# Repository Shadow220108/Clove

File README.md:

<h1 align="center">
  <br>

  <br>
  Clove
  <br>
</h1>
<h3 align="center">
First ever paw shaped tamagotchi, with 4 buttons, LEDs, screen and battery 
</h3>

| Render | 
| --- |
|  | 

The case is made to be paw shaped, designed in two halves which are supposed to be put together with 4 different M3x8mm screws.  
It has a slot to hold the battery, 4 screw holes to hold and tighten the PCB! The top case features 4 holes for the buttons and 
a space for the screen.  

| Zine |
| --- |
| .png) |

## PCB Design 
|  |
|--- |  

 The PCB is 2 layers with dimensions under 100 by 100mm, it is designed to be in a paw shape has some cool 
 silkscreen with red color, cause red colored PCBs are cool.  

 ### All the PCB files are [here](https://github.com/Shadow220108/Clove/tree/main/PCB) 

| PCB design |
| --- |
| .png) | .png) |

## Schematics  

Here are the schematic designs,

| Schematics |
| --- |
|  |

## Why was it made?  

It was made for fallout hackclub with the amazing guide made by @Tanuki ( huge credits to him ) 

## How you can get one for yourself? 

That is pretty easy, 

1. Order all the parts going through the BOM
2. Start by soldering all the components on to the PCB
3. Put the buttons in the holes, screw the PCB to the case and screw both the halves together
4. Flash the Xiao with firmware and boom
5. Start playing with your tamagotchi

## BOM  

|Product                       |Description                                      |Quantity   |Unit Price  |Link      |Total cost ( Including Shipping )|
|------------------------------|-------------------------------------------------|-----------|------------|----------|---------------------------------|
|                              |                                                 |           |            |          |                                 |
|PCB                           |to connect and hold all the electronic components|5 ( MOQ )  |2$          |[Link](https://cart.jlcpcb.com/shopcart/cart/)      |12.31$                           |
|Xiao ESP32C6                  |MCU for running the screen                       |1          |7.79$       |[Link](https://robu.in/product/seeed-studio-xiao-esp32c6/)      |8.32$                            |
|0.96" OLED                    |Main display                                     |1          |1.69$       |[Link](https://robocraze.com/products/0-96in-oled-display-module-4pin?variant=40192586645657&country=IN&currency=INR&utm_medium=product_sync&utm_source=google&utm_content=sag_organic&utm_campaign=sag_organic)      |2.22$                            |
|Tactile Switch buttons (6x6mm)|To control the character                         |10 ( MOQ ) |0.10$       |[Link](https://robu.in/product/6x6x5-tactile-push-button-switch/)      |0.10$                            |
|M3x5mm Heastset Inserts       |To hold downt the top and bottom case            |8          |0.10$       |[Link](https://onlyscrews.in/products/hex-allen-csk-m3-x-8-screw-pack-of-20)      |1.50$                            |
|M3x8mm Screws                 |To hold downt the top and bottom case            |8          |0.20$       |[Link](https://onlyscrews.in/products/hex-allen-csk-m3-x-8-screw-pack-of-20)      |0.20$                            |
|Buzzer                        |to make some sounds                              |1          |0.48$       |[Link](https://robu.in/product/1-month-warranty-1248/)      |0.48$                            |
|LiPo Battery                  |To power everything!                             |1          |1.65$       |[Link](https://robu.in/product/wly502025-200mah-3-7v-single-cell-rechargeable-lipo-battery/)      |1.65$                            |
|LEDs                          |They light up                                    |12         |Self sourced|          |                                 |
|Resistors                     |for the battery voltage                          |2          |Self sourced|          |                                 |
|                              |                                                 |           |            |Total cost|26.78                            |

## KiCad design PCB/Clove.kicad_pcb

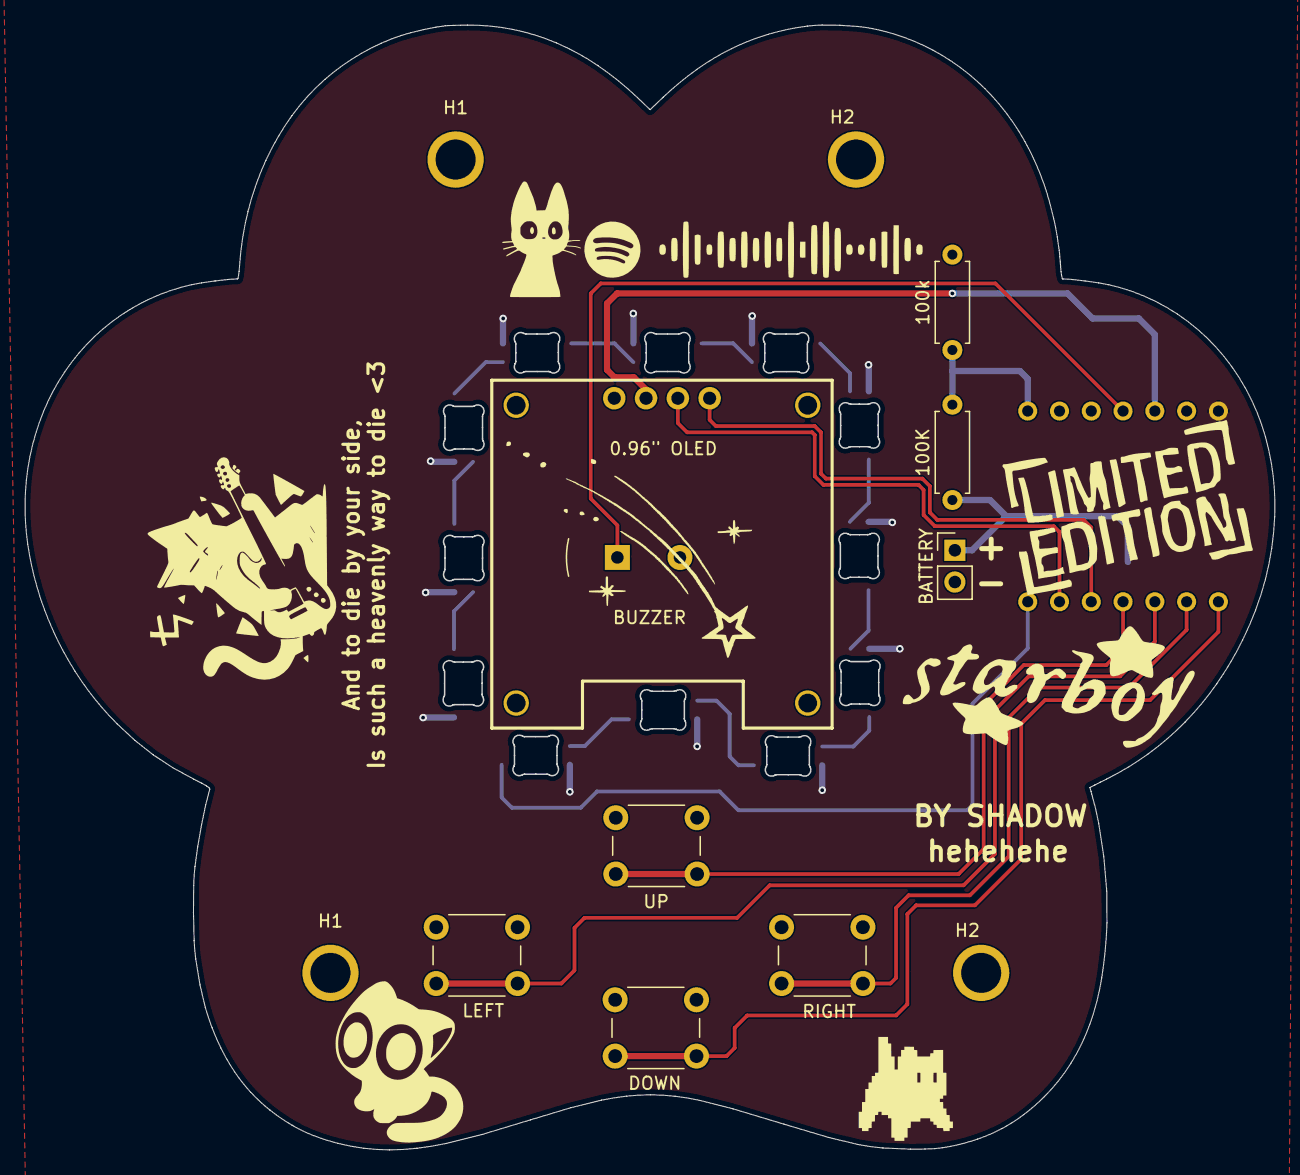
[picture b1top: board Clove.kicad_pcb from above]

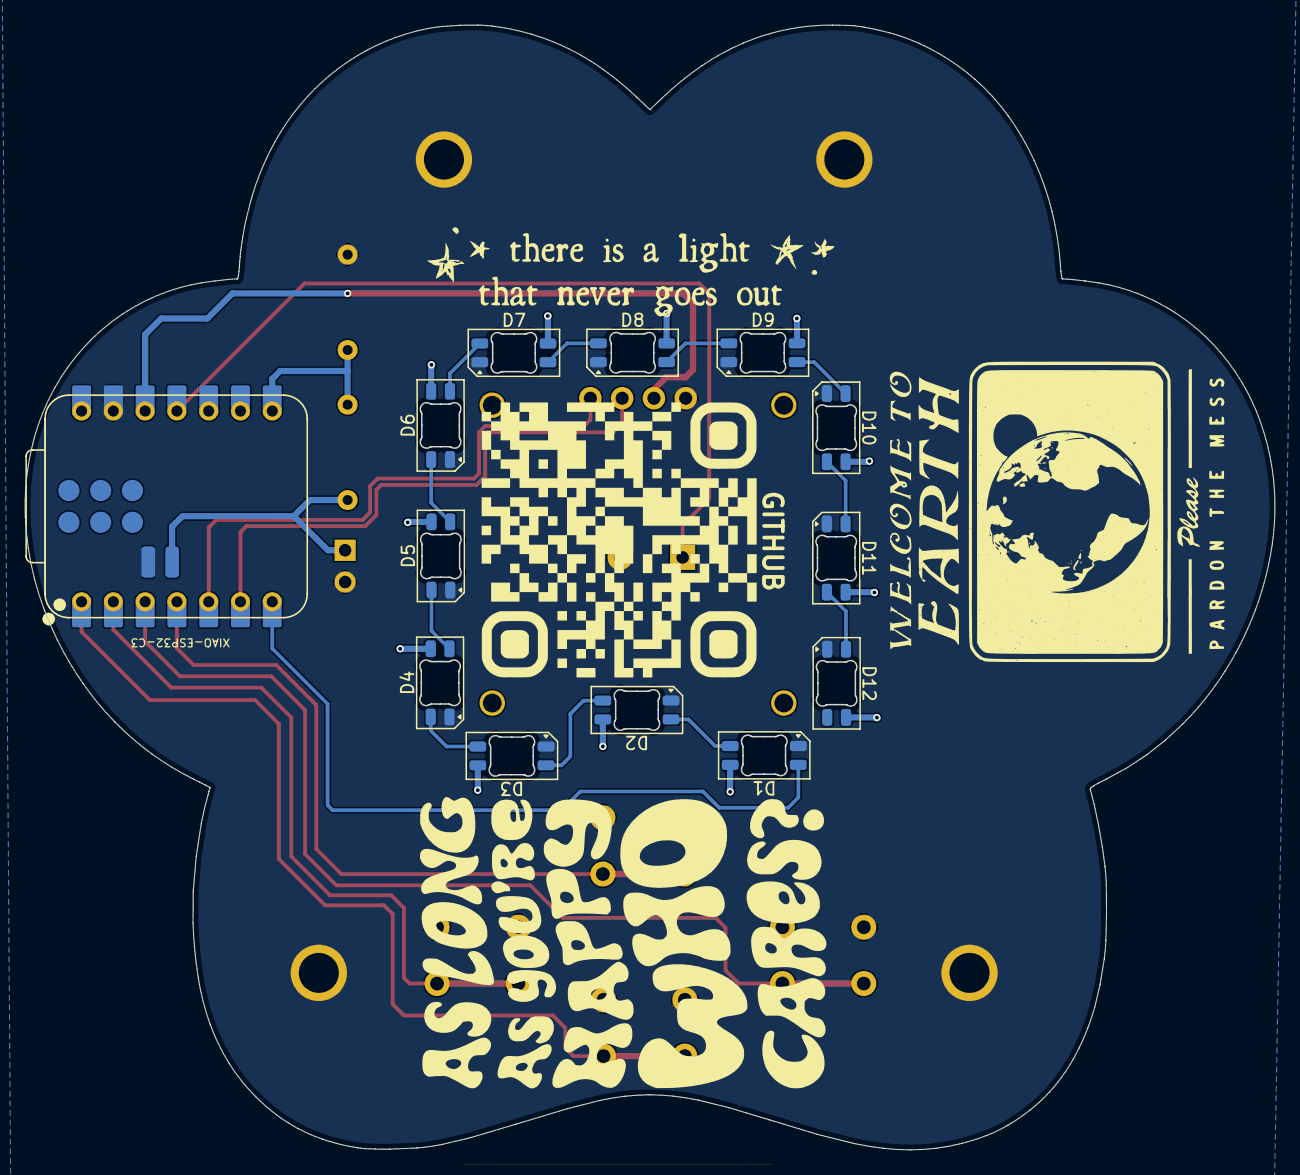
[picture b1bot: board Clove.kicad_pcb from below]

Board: 2 copper layers, 99.8 x 89.8 mm, 26 parts (13 on the bottom side), 24 nets.

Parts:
0.96" OLED: 0.96" OLED; OLED-TH_L27.8-W27.2-P2.54_C9900033791
100K, 100k: 100k; R_Axial_DIN0207_L6.3mm_D2.5mm_P7.62mm_Horizontal
BATTERY: Battery; PinHeader_1x02_P2.54mm_Vertical
BUZZER: Buzzer; Buzzer_TDK_PS1240P02BT_D12.2mm_H6.5mm
D1, D2, D3, D4, D5, D6, D7, D8, D9, D10, D11, D12: SK6812MINI-E; LED_SK6812MINI-E_3.2x2.8mm_P1.5mm_ReverseMount
DOWN: DOWN; SW_PUSH_6mm_H4.3mm
H1, H1#2, H2, H2#2: MountingHole_Pad; MountingHole_3.2mm_M3_Pad
LEFT: LEFT; SW_PUSH_6mm_H4.3mm
RIGHT: RIGHT; SW_PUSH_6mm_H4.3mm
UP: UP; SW_PUSH_6mm_H4.3mm
XIAO-ESP32-C3: XIAO-ESP32-C3-SMD; XIAO-ESP32-C3-DIP-SMD

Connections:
+3V3: 0.96" OLED.2 (VCC), XIAO-ESP32-C3.12 (3V3)
+5V: D1.3 (VDD), D2.3 (VDD), D3.3 (VDD), D4.3 (VDD), D5.3 (VDD), D6.3 (VDD), D7.3 (VDD), D8.3 (VDD), D9.3 (VDD), D10.3 (VDD), D11.3 (VDD), D12.3 (VDD), XIAO-ESP32-C3.14 (VBUS)
+BATT: 100K.1, BATTERY.1, XIAO-ESP32-C3.21 (BAT)
/BATTERY: 100K.2, 100k.1, XIAO-ESP32-C3.8 (GPIO20_D7_RX)
/BUZZER: BUZZER.1 (+), XIAO-ESP32-C3.11 (GPIO10_D10_MOSI)
/DOWN: DOWN.2, XIAO-ESP32-C3.1 (GPIO2_A0_D0)
/LED: D1.2 (DIN), XIAO-ESP32-C3.7 (GPIO21_D6_TX)
/LEFT: LEFT.2, XIAO-ESP32-C3.3 (GPIO4_A2_D2)
/RIGHT: RIGHT.2, XIAO-ESP32-C3.2 (GPIO3_A1_D1)
/SCL: 0.96" OLED.3 (SCL), XIAO-ESP32-C3.6 (GPIO7_D5_SCL)
/SDA: 0.96" OLED.4 (SDA), XIAO-ESP32-C3.5 (GPIO6_D4_SDA)
/UP: UP.2, XIAO-ESP32-C3.4 (GPIO5_A3_D3)
GND: 0.96" OLED.1 (GND), 100k.2, BATTERY.2, BUZZER.2 (-), D1.1 (VSS), D2.1 (VSS), D3.1 (VSS), D4.1 (VSS), D5.1 (VSS), D6.1 (VSS), D7.1 (VSS), D8.1 (VSS), D9.1 (VSS), D10.1 (VSS), D11.1 (VSS), D12.1 (VSS), DOWN.1, H1.1 (1_1), H1#2.1 (1_1), H2.1 (1_1), H2#2.1 (1_1), LEFT.1, RIGHT.1, UP.1, XIAO-ESP32-C3.13 (GND), XIAO-ESP32-C3.22 (GND)
unnamed: D1.4 (DOUT), D2.2 (DIN)
unnamed: D2.4 (DOUT), D3.2 (DIN)
unnamed: D3.4 (DOUT), D4.2 (DIN)
unnamed: D4.4 (DOUT), D5.2 (DIN)
unnamed: D5.4 (DOUT), D6.2 (DIN)
unnamed: D6.4 (DOUT), D7.2 (DIN)
unnamed: D7.4 (DOUT), D8.2 (DIN)
unnamed: D8.4 (DOUT), D9.2 (DIN)
unnamed: D9.4 (DOUT), D10.2 (DIN)
unnamed: D10.4 (DOUT), D11.2 (DIN)
unnamed: D11.4 (DOUT), D12.2 (DIN)

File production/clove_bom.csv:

Designator,Footprint,Quantity,Value,LCSC Part #
"0.96"" OLED",OLED-TH_L27.8-W27.2-P2.54_C9900033791,1,"0.96"" OLED",C5248080
"100K_2, 100K",R_Axial_DIN0207_L6.3mm_D2.5mm_P7.62mm_Horizontal,2,100k,
BATTERY,PinHeader_1x02_P2.54mm_Vertical,1,Battery,
BUZZER,Buzzer_TDK_PS1240P02BT_D12.2mm_H6.5mm,1,Buzzer,
"D1, D10, D11, D12, D2, D3, D4, D5, D6, D7, D8, D9",LED_SK6812MINI-E_3.2x2.8mm_P1.5mm_ReverseMount,12,SK6812MINI-E,
DOWN,SW_PUSH_6mm_H4.3mm,1,DOWN,
LEFT,SW_PUSH_6mm_H4.3mm,1,LEFT,
RIGHT,SW_PUSH_6mm_H4.3mm,1,RIGHT,
UP,SW_PUSH_6mm_H4.3mm,1,UP,
XIAO-ESP32-C3,XIAO-ESP32-C3-DIP-SMD,1,XIAO-ESP32-C3-SMD,

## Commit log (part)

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2026-06-21 Adding more files
2026-06-21 Zine
